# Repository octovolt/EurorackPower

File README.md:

# EurorackPower

A submodule PCB for prototyping Eurorack modules. This PCB encapsulates the circuit often used in Eurorack modules for reverse polarity protection and ripple filtering. This PCB can be mounted onto another PCB or onto a breadboard. 

To mount the EurorackPower submodule on a breadboard, you can do one of two things:

1. Only use the pairs of pins on the left side of the board to connect to the power rails of the breadboard. This is a flimsy solution, but it can work.
2. Only solder two of the three pins in the top right and bottom right corners, making them match the pins on the left side. This allows you to connect the EurorackPower submodule to the power rails of the breadboard with all four sets of pins making it much more stable.

```
Q. Why are there three pins on the right corners at all? 
A. Providing +12v, ground and -12v at both corners
   makes it easier to develop PCBs
   to which this submodule would provide power.
```

The PCB conforms to an as-yet-unnamed system of submodules I am developing to make prototyping a little bit easier and more modular. Yeah, modular in your modular.

When soldering, please see the [interactive BOM](https://octovolt.github.io/EurorackPower/).

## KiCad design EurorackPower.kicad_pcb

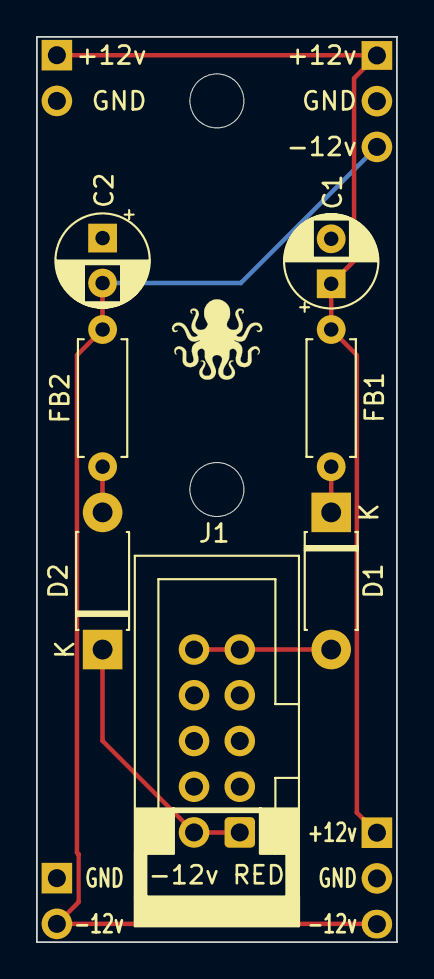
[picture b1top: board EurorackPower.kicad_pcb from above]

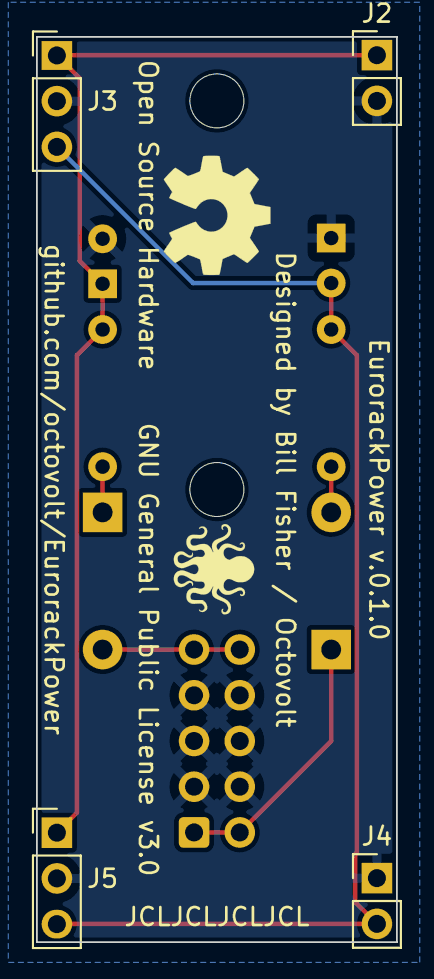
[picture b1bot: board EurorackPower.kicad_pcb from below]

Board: 2 copper layers, 20.0 x 50.3 mm, 16 parts (6 on the bottom side), 7 nets.

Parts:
C1, C2: 10u; CP_Radial_D5.0mm_P2.50mm
D1, D2: 1n400x; D_DO-41_SOD81_P7.62mm_Horizontal
FB1, FB2: Ferrite Bead; R_Axial_DIN0207_L6.3mm_D2.5mm_P7.62mm_Horizontal
H1, H2: MountingHole; MountingHole_3mm
J1: europower; IDC-Header_2x05_P2.54mm_Vertical
J2, J4: Conn_01x02; PinHeader_1x02_P2.54mm_Vertical
J3, J5: Conn_01x03; PinHeader_1x03_P2.54mm_Vertical
OA1, OA2: Octopus_Arts_Logo; octopus_silk_screen
OSHW1: Logo_Open_Hardware_Large; OSHW-Symbol_6.7x6mm_SilkScreen

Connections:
+12v: C1.1, FB1.2, J2.1, J3.1, J5.1
-12v: C2.2, FB2.2, J3.3, J4.2, J5.3
GND: C1.2, C2.1, J1.3, J1.4, J1.5, J1.6, J1.7, J1.8, J2.2, J3.2, J4.1, J5.2
unnamed: D1.1 (K), FB1.1
unnamed: D1.2 (A), J1.9, J1.10
unnamed: D2.1 (K), J1.1, J1.2
unnamed: D2.2 (A), FB2.1

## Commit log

2023-12-30 More details in README.md
2023-12-30 Moar details in README.md
2023-12-30 formatting README.md
2023-12-30 more formatting of the README.md
2023-12-30 images
2023-12-30 Update README.md with 2nd image
2023-12-30 bom and schematic
2023-12-30 move interactive bom to docs directory
2023-12-30 fake commit to force page compilation
2023-12-30 rename ibom.html to index.html
2023-12-30 get interactive bom to work
2023-12-30 link to interactive bom in README.md

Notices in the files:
EurorackPower.kicad_pcb:
GNU General Public License v3.0
